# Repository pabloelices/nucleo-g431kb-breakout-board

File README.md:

# nucleo-g431kb-breakout-board

## License

MIT License. See [LICENSE](LICENSE "LICENSE") for details.

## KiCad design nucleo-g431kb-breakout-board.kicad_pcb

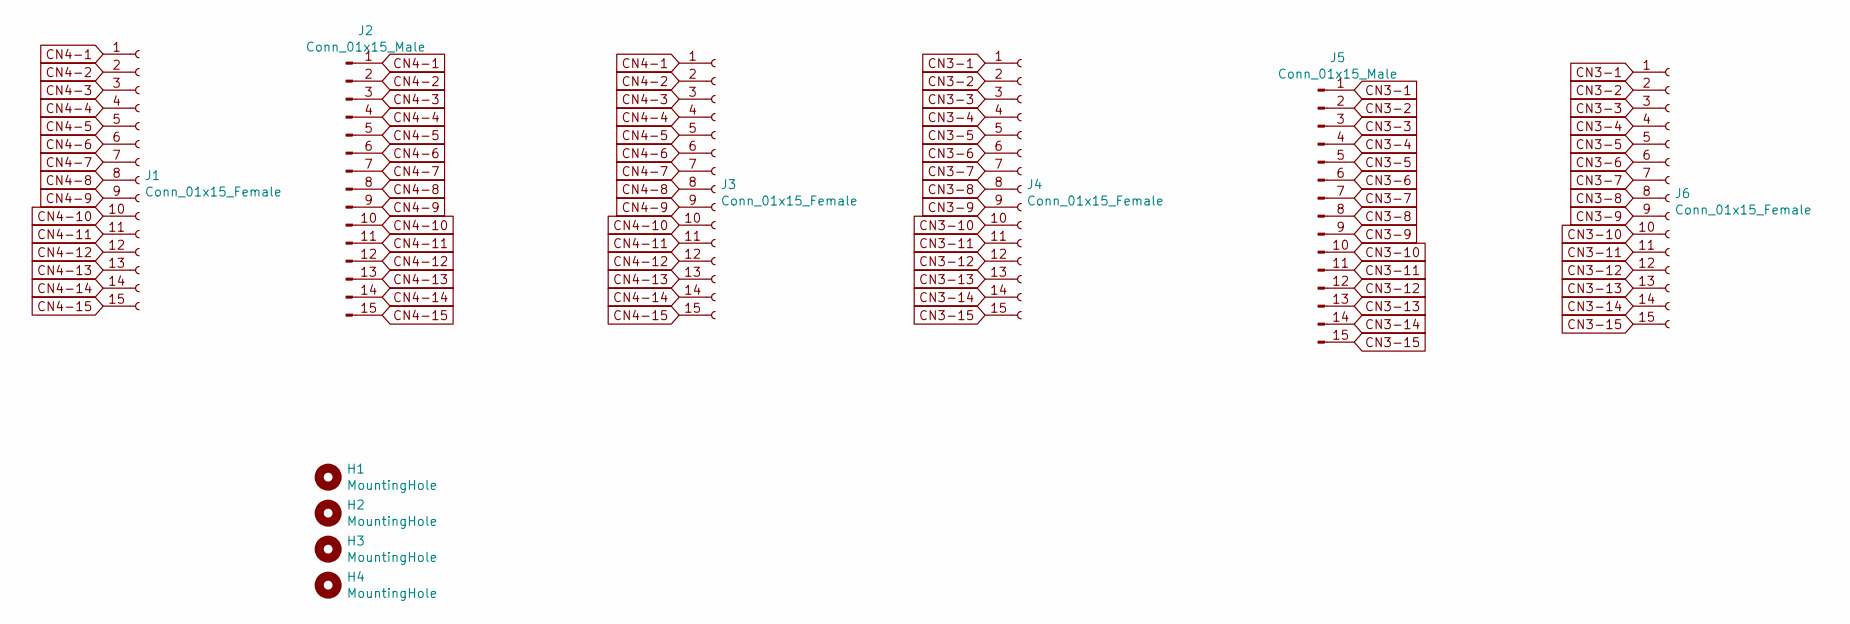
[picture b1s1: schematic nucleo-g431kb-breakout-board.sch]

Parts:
H1, H2, H3, H4: MountingHole; MountingHole_2.7mm_M2.5
J1, J3, J4, J6: Conn_01x15_Female; PinSocket_1x15_P2.54mm_Vertical
J2, J5: Conn_01x15_Male; PinHeader_1x15_P2.54mm_Vertical

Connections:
CN3-1: J4.1, J5.1, J6.1
CN3-2: J4.2, J5.2, J6.2
CN3-3: J4.3, J5.3, J6.3
CN3-4: J4.4, J5.4, J6.4
CN3-5: J4.5, J5.5, J6.5
CN3-6: J4.6, J5.6, J6.6
CN3-7: J4.7, J5.7, J6.7
CN3-8: J4.8, J5.8, J6.8
CN3-9: J4.9, J5.9, J6.9
CN3-10: J4.10, J5.10, J6.10
CN3-11: J4.11, J5.11, J6.11
CN3-12: J4.12, J5.12, J6.12
CN3-13: J4.13, J5.13, J6.13
CN3-14: J4.14, J5.14, J6.14
CN3-15: J4.15, J5.15, J6.15
CN4-1: J1.1, J2.1, J3.1
CN4-2: J1.2, J2.2, J3.2
CN4-3: J1.3, J2.3, J3.3
CN4-4: J1.4, J2.4, J3.4
CN4-5: J1.5, J2.5, J3.5
CN4-6: J1.6, J2.6, J3.6
CN4-7: J1.7, J2.7, J3.7
CN4-8: J1.8, J2.8, J3.8
CN4-9: J1.9, J2.9, J3.9
CN4-10: J1.10, J2.10, J3.10
CN4-11: J1.11, J2.11, J3.11
CN4-12: J1.12, J2.12, J3.12
CN4-13: J1.13, J2.13, J3.13
CN4-14: J1.14, J2.14, J3.14
CN4-15: J1.15, J2.15, J3.15

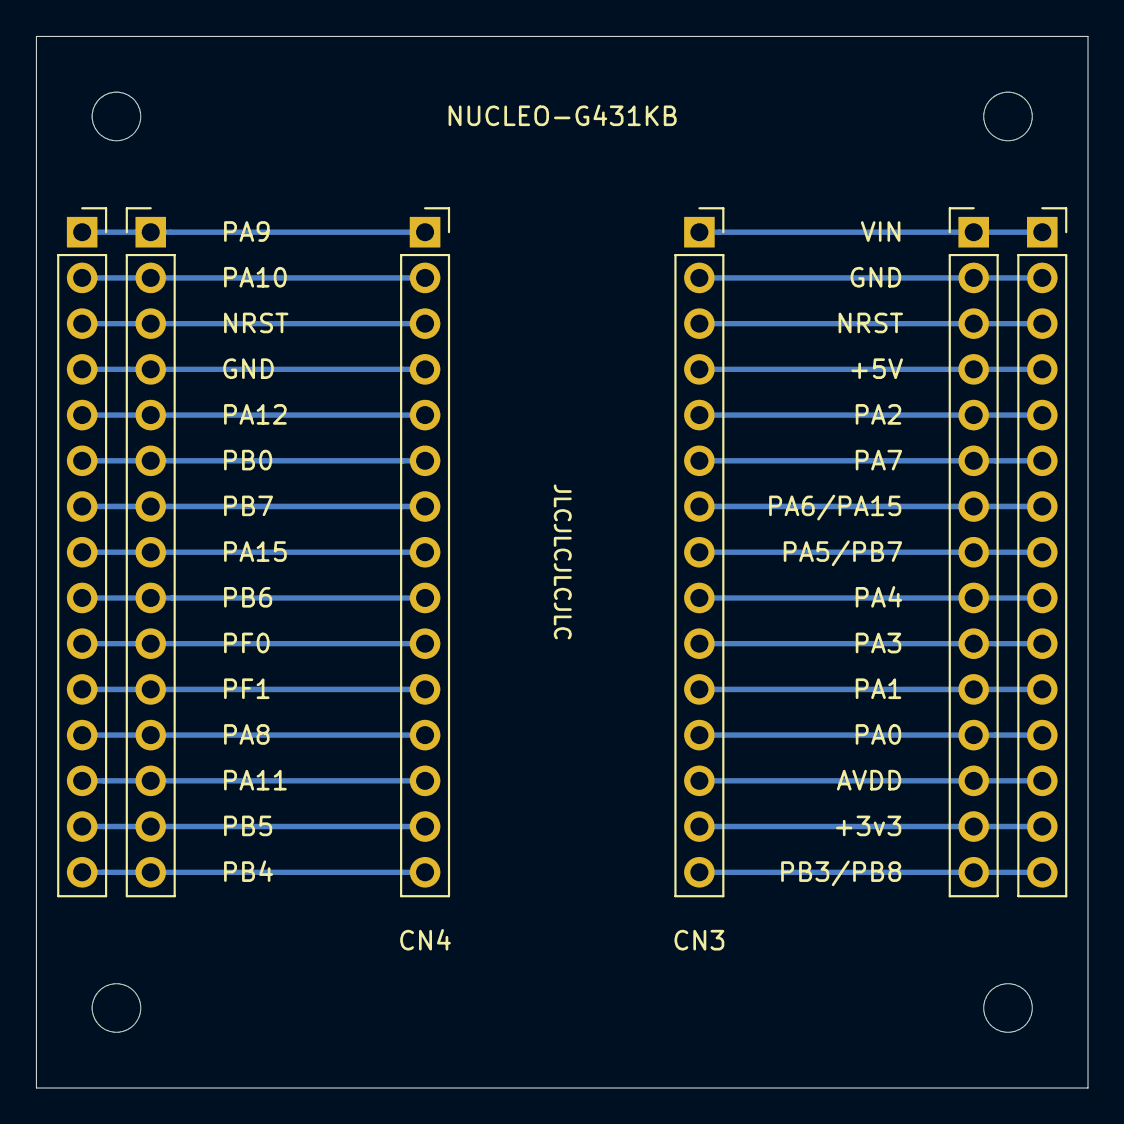
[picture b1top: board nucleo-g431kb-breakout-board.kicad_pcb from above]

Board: 2 copper layers, 58.4 x 58.4 mm, 10 parts (0 on the bottom side), 30 nets.
